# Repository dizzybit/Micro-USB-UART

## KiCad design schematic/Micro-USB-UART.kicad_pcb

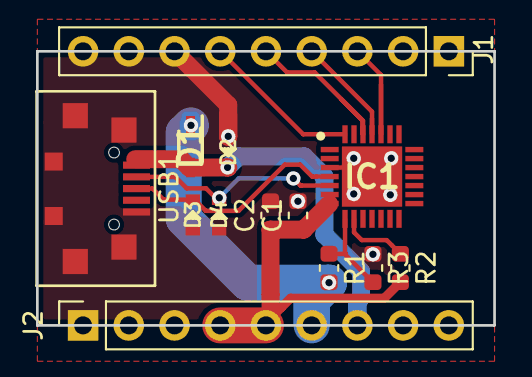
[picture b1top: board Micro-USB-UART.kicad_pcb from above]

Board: 2 copper layers, 25.4 x 15.2 mm, 14 parts (1 on the bottom side), 12 nets.

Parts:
C1: C4.7uF/6.3V(20%); C_0603_1608Metric
C2: C0.1uF/50V(10%); C_0603_1608Metric
D1: BAT760,115; SOD2513X120N
D2, D3, D4: T5V0S5-7; SOD-523
IC1: CP2102N-A01-GQFN28R; QFN50P500X500X80-29N-D
J1, J2: Conn_01x09; PinSocket_1x09_P2.54mm_Vertical
R1: R22.1K(1%); C_0603_1608Metric
R2: R2Kohm(5%); R_0603_1608Metric
R3: R47.5K(1%); C_0603_1608Metric
U1: DizzyBITLogo; DizzyBIT_silk_20
USB1: USB_B_Micro; DS1105-12

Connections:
+3.3V: C1.1, C2.1, IC1.6, IC1.7, J2.4, J2.5, R2.2
DTR: IC1.28, J1.6
EXT_5V: D1.1, J2.6, R1.2
GND: C1.2, C2.2, D2.2, D3.2, D4.2, IC1.3, IC1.29, J1.1, J1.2, J1.7, J1.8, J1.9, J2.1, J2.2, J2.3, J2.8, J2.9, R3.1, USB1.5, USB1.6
IO1: IC1.25, J1.4
IO3: IC1.26, J1.5
unnamed: IC1.8, R1.1, R3.2
unnamed: IC1.9, R2.1
RTS: IC1.24, J1.3
USB_DN: D4.1, IC1.5, USB1.2
USB_DP: D3.1, IC1.4, USB1.3
VBUS: D1.2, D2.1, J2.7, USB1.1

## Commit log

2019-10-02 UART to MicroUSB adapter
2019-10-04 Added 3D and Gerber files
